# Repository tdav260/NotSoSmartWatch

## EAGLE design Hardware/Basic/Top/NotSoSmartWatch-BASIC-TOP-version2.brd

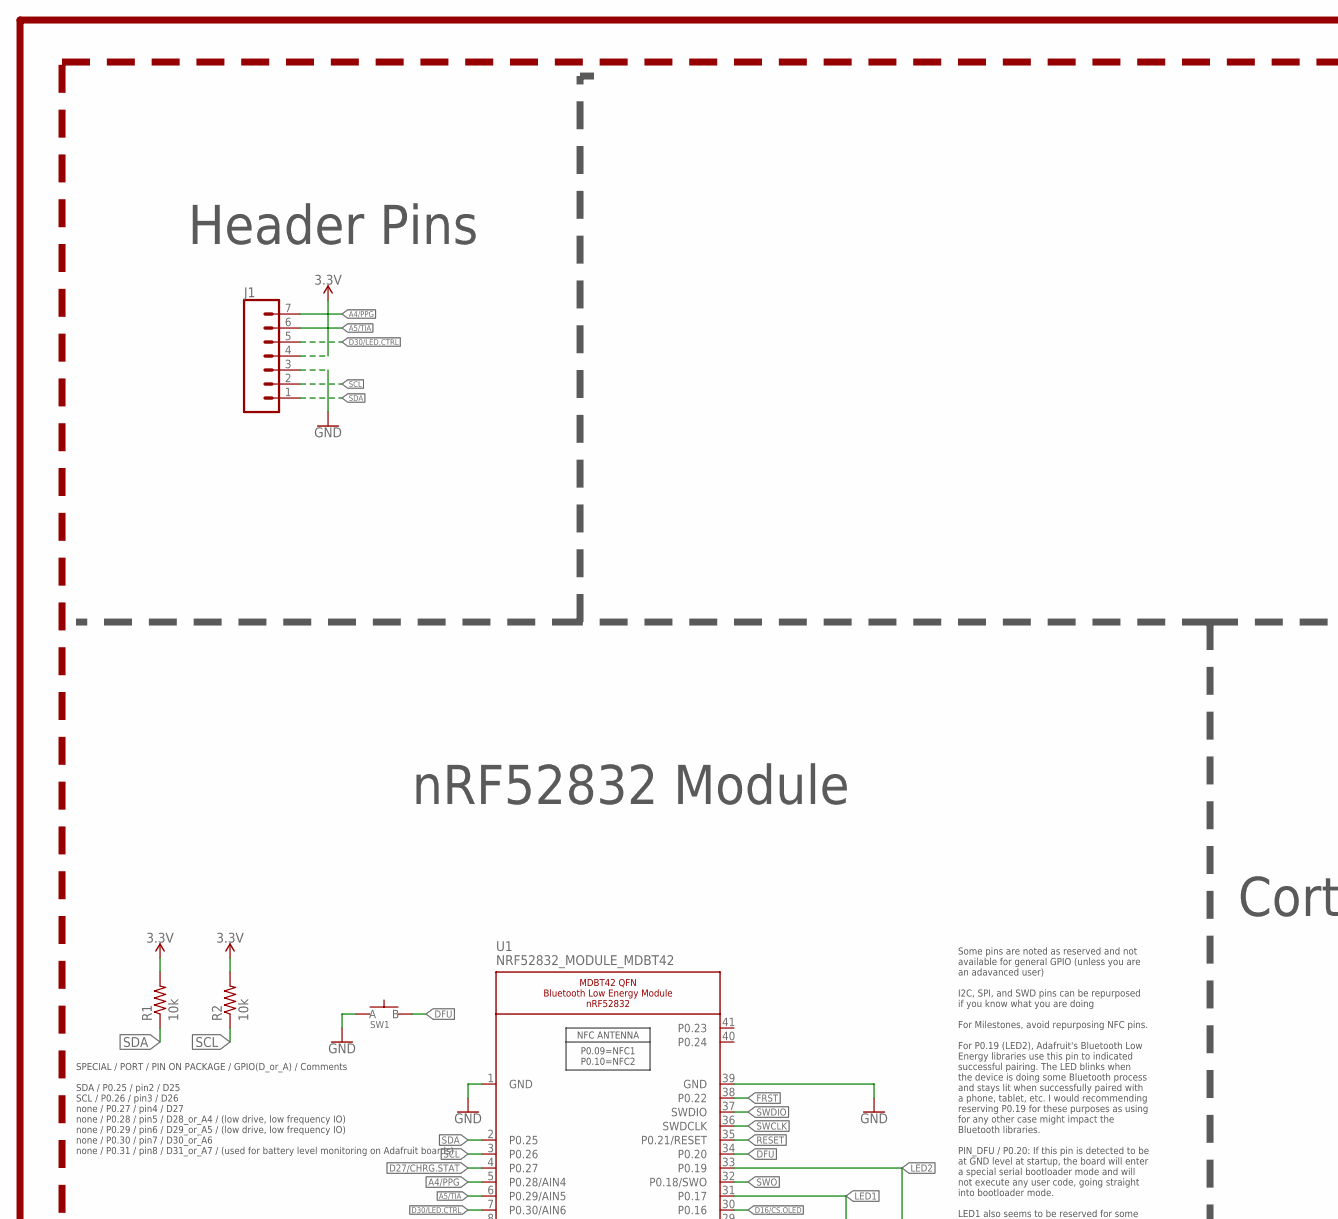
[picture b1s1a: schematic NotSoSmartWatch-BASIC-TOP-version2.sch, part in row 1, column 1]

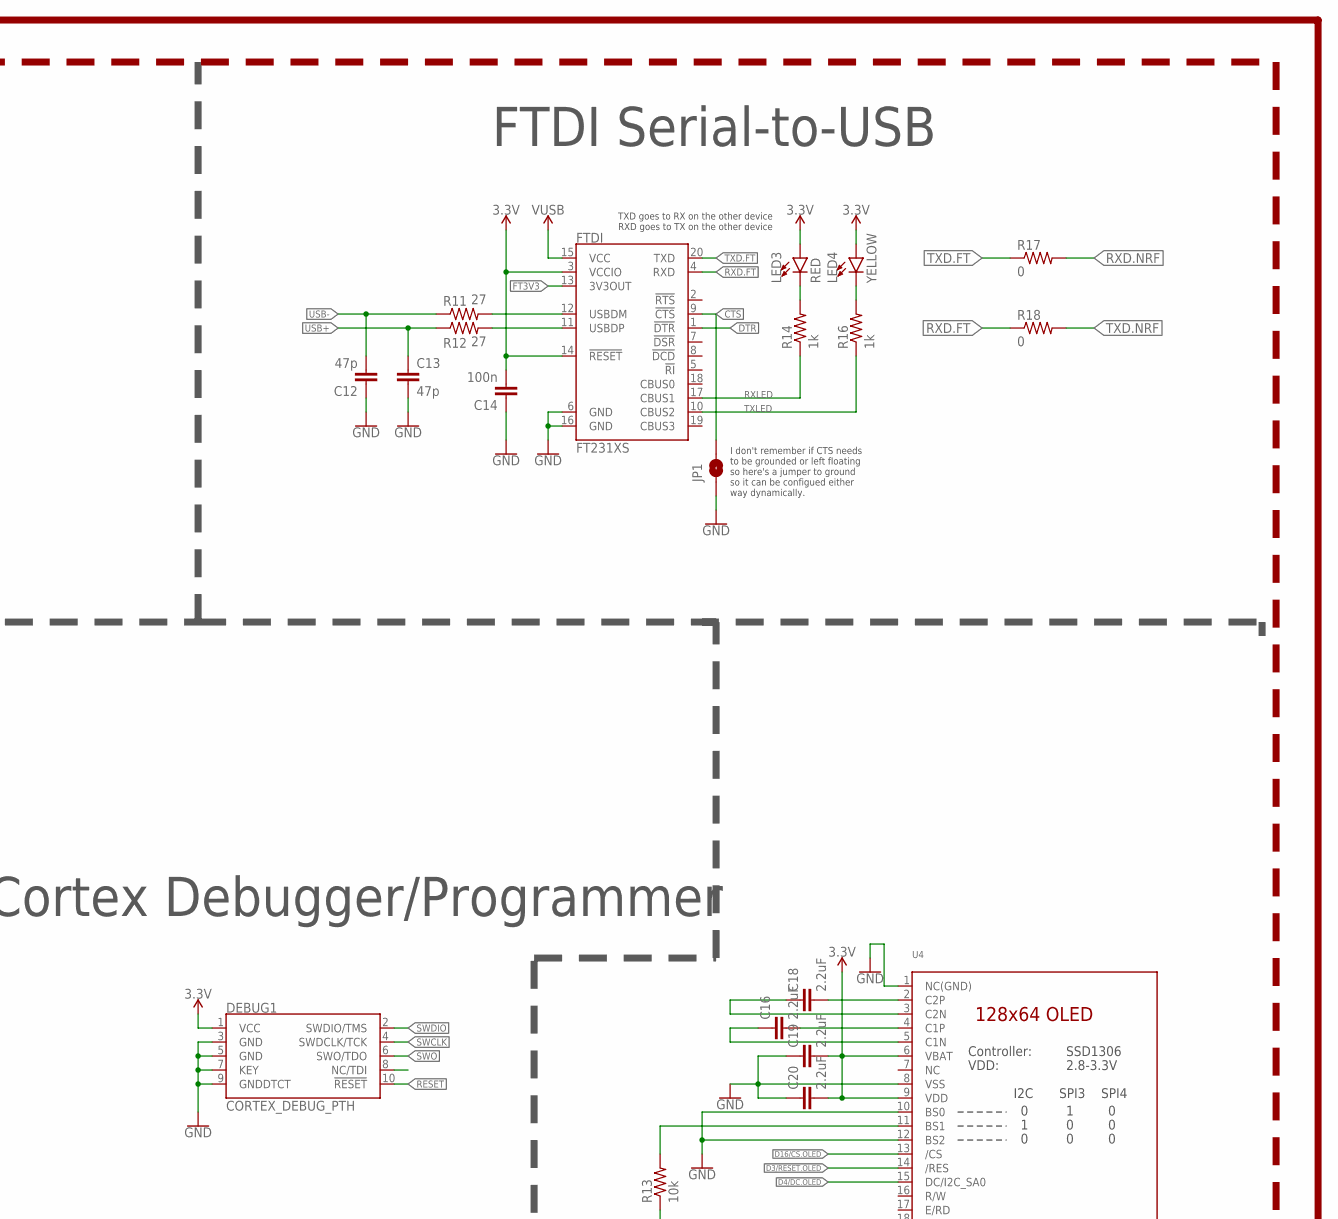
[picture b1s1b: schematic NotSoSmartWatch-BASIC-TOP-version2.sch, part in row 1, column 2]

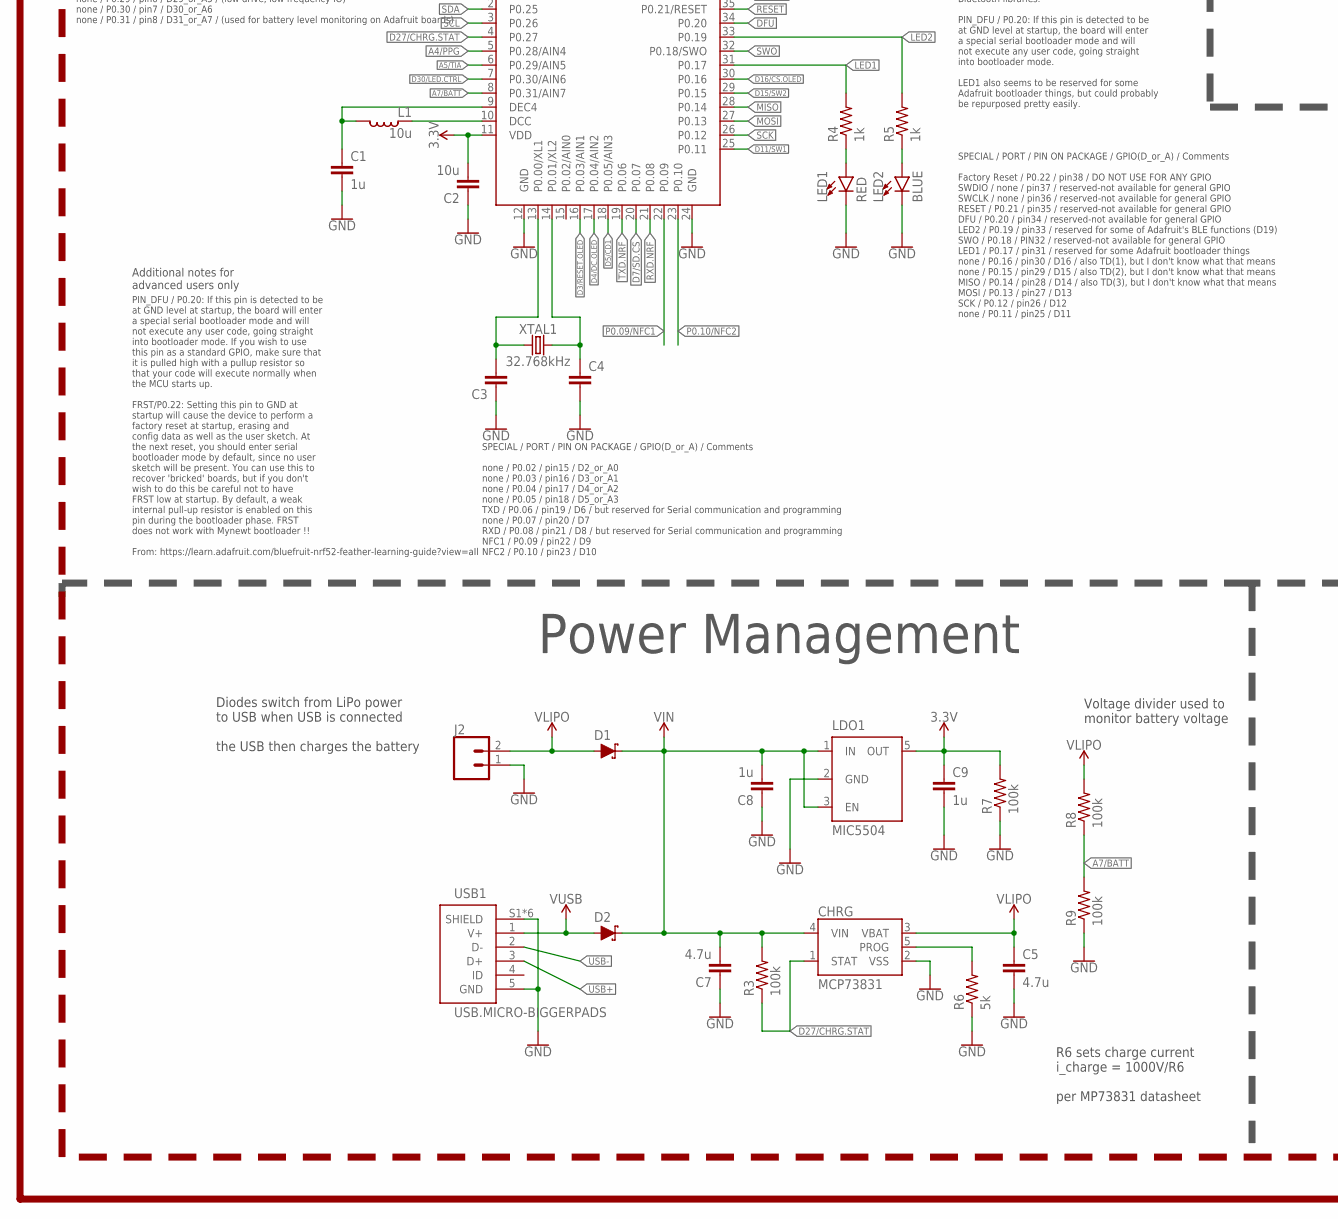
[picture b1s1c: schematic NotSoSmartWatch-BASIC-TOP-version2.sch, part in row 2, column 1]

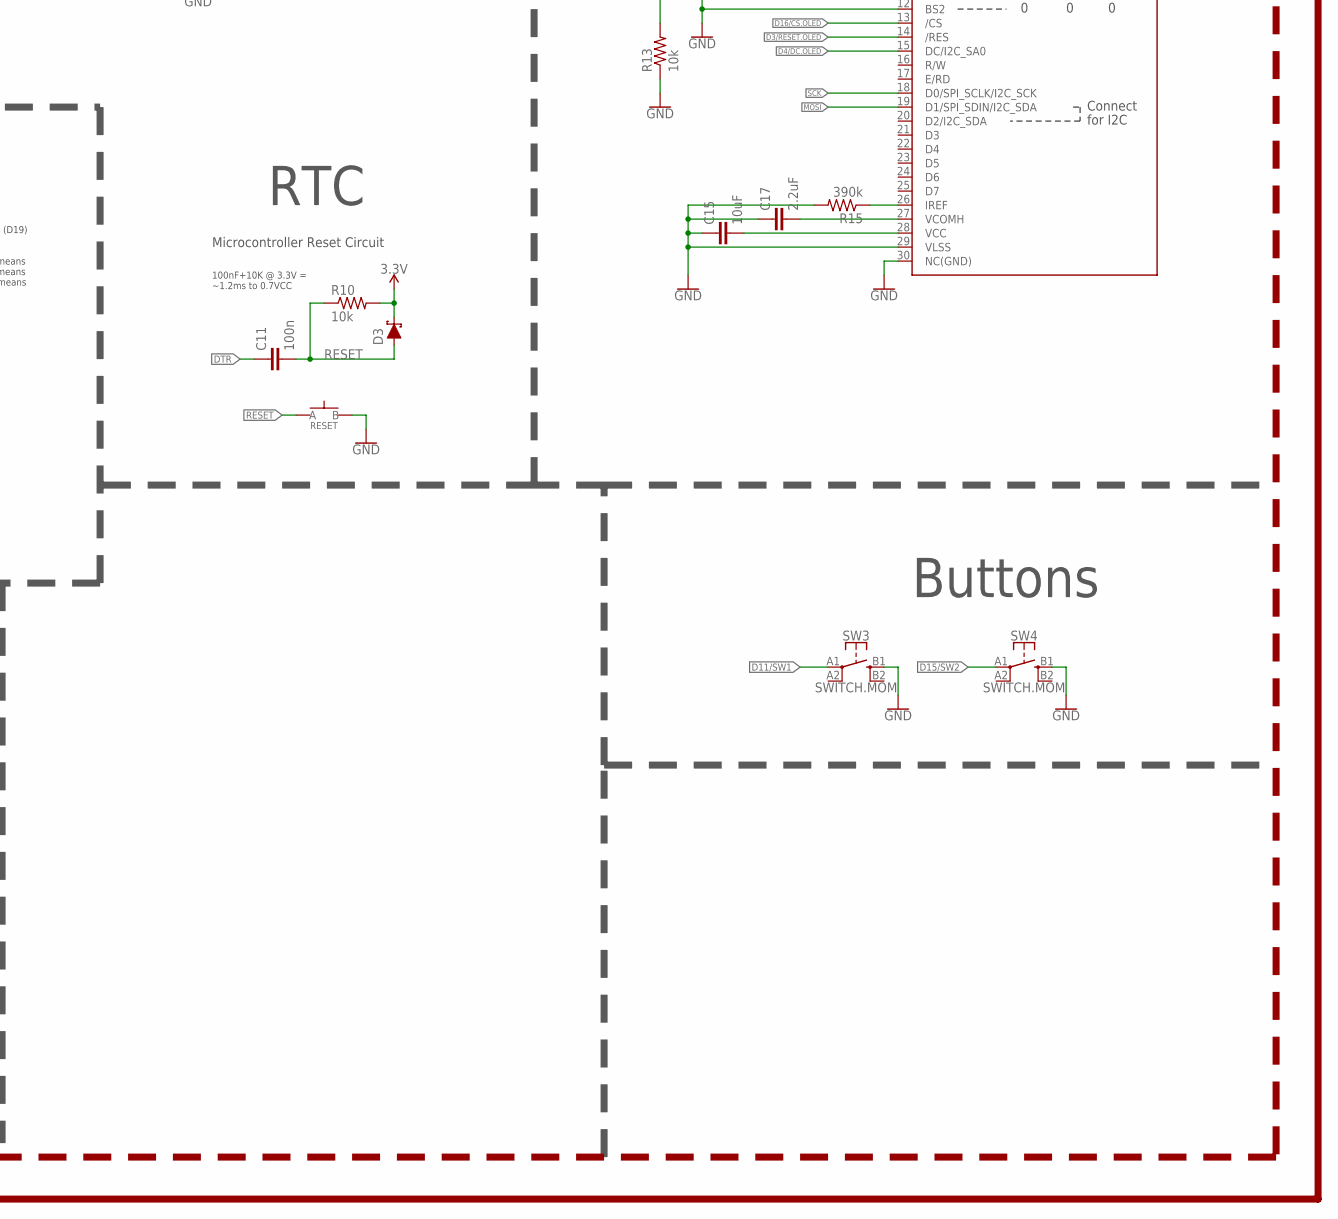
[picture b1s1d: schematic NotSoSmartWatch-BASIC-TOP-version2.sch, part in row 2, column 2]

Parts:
C1, C8, C9: 1u; C0603
C2: 10u; C0805
C3, C4: CAPACITOR0603; C0603
C5, C7: 4.7u; C0603
C11, C14: 100n; C0603
C12, C13: 47p; C0603
C15: 10uF; C0603
C16, C18, C19, C20: 2.2uF; C0402
C17: 2.2uF; C0603
CHRG: MCP73831; SOT23-5
D1, D2, D3: SCHOTTKY-USC; USC
DEBUG1: CORTEX_DEBUG_PTH; 2X5-PTH-1.27MM
FTDI: FT231XS; SSOP20_L
J1: CONN_07-1.27MM; 1X07_1.27MM
J2: CONN_02; 1X02
JP1: JUMPER-SMT_2_NO_SILK; SMT-JUMPER_2_NO_SILK
L1: 10u; L0603
LDO1: MIC5504; SOT23-5
LED1, LED3: RED; LED-0603
LED2: BLUE; LED-0603
LED4: YELLOW; LED-0603
R1, R2, R10, R13: 10k; R0603
R3, R7, R8, R9: 100k; R0603
R4, R5, R14, R16: 1k; R0603
R6: 5k; R0603
R11, R12: 27; R0603
R15: 390k; R0603
R17, R18: 0; R0603
RESET: SPST-PTS830GG140-COPY.1-3; BUTTON-GULLWING
SW1: SPST-PTS830GG140-COPY.1-3; BUTTON-GULLWING
SW3, SW4: SWITCH.MOM; TACTILE_SWITCH_SMD_6.2MM_TALL
U1: NRF52832_MODULE_MDBT42; BLE_MODULE_RAYTAC_MDBT42
U4: DISP_OLED_UG-2864HSWEG01-NO-WRAPAROUND; UG-2864HSWEG01_0.96IN_NO-WRAPAROUND
USB1: USB.MICRO-BIGGERPADS; USB-MICRO-01.BIGGERPADS
XTAL1: 32.768kHz; 2-SMD.NOLEAD.2.0MMTO1.2MM

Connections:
3.3V: C2.2, C9.1, C14.2, C19.2, C20.2, D3.- (C), DEBUG1.1 (VCC), FTDI.3 (VCCIO), FTDI.14 (!RESET), J1.4, LDO1.5 (OUT), LED3.A, LED4.A, R1.2, R2.2, R7.2, R10.2, U1.11 (VDD), U4.6 (VBAT), U4.9 (VDD)
A4/PPG: J1.7, U1.5 (P0.28/AIN4)
A5/TIA: J1.6, U1.6 (P0.29/AIN5)
A7/BATT: R8.1, R9.2, U1.8 (P0.31/AIN7)
CTS: FTDI.9 (!CTS), JP1.2
D3/RESET.OLED: U1.16 (P0.03/AIN1), U4.14 (/RES)
D4/DC.OLED: U1.17 (P0.04/AIN2), U4.15 (DC/I2C_SA0)
D5/CD1: U1.18 (P0.05/AIN3)
D7/SD.CS: U1.20 (P0.07)
D11/SW1: SW3.A1 (1), U1.25 (P0.11)
D15/SW2: SW4.A1 (1), U1.29 (P0.15)
D16/CS.OLED: U1.30 (P0.16), U4.13 (/CS)
D27/CHRG.STAT: CHRG.1 (STAT), R3.1, U1.4 (P0.27)
D30/LED.CTRL: J1.5, U1.7 (P0.30/AIN6)
DFU: SW1.3 (B), U1.34 (P0.20)
DTR: C11.1, FTDI.1 (!DTR)
FRST: U1.38 (P0.22)
FT3V3: FTDI.13 (3V3OUT)
GND: C1.2, C2.1, C3.1, C4.2, C5.2, C7.1, C8.1, C9.2, C12.1, C13.2, C14.1, C15.1, C17.1, C19.1, C20.1, CHRG.2 (VSS), DEBUG1.3 (GND), DEBUG1.5 (GND), DEBUG1.7 (KEY), DEBUG1.9 (GNDDTCT), FTDI.6 (GND), FTDI.16 (GND), J1.3, J2.1, JP1.1, LDO1.2 (GND), LED1.C, LED2.C, R6.1, R7.1, R9.1, R13.1, R15.2, RESET.3 (B), SW1.1 (A), SW3.B1 (3), SW4.B1 (3), U1.1 (GND), U1.12 (GND), U1.24 (GND), U1.39 (GND), U4.1 (NC(GND)), U4.8 (VSS), U4.10 (BS0), U4.12 (BS2), U4.29 (VLSS), U4.30 (NC(GND)), USB1.5 (GND), USB1.S1 (SHIELD), USB1.S2 (SHIELD), USB1.S3 (SHIELD), USB1.S4 (SHIELD), USB1.S5 (SHIELD), USB1.S6 (SHIELD)
LED1: R4.2, U1.31 (P0.17)
LED2: R5.2, U1.33 (P0.19)
MISO: U1.28 (P0.14)
MOSI: U1.27 (P0.13), U4.19 (D1/SPI_SDIN/I2C_SDA)
unnamed: R13.2, U4.11 (BS1)
unnamed: R15.1, U4.26 (IREF)
unnamed: C18.2, U4.2 (C2P)
unnamed: C3.2, U1.13 (P0.00/XL1), XTAL1.P$1 (1)
unnamed: C18.1, U4.3 (C2N)
unnamed: C4.1, U1.14 (P0.01/XL2), XTAL1.P$2 (2)
unnamed: C16.2, U4.4 (C1P)
unnamed: C16.1, U4.5 (C1N)
unnamed: LED1.A, R4.1
unnamed: LED2.A, R5.1
unnamed: L1.1, U1.10 (DCC)
unnamed: C1.1, L1.2, U1.9 (DEC4)
unnamed: C15.2, U4.28 (VCC)
unnamed: C17.2, U4.27 (VCOMH)
unnamed: CHRG.5 (PROG), R6.2
unnamed: FTDI.12 (USBDM), R11.2
unnamed: FTDI.11 (USBDP), R12.2
unnamed: LED3.C, R14.2
unnamed: LED4.C, R16.2
P0.09/NFC1: U1.22 (P0.09)
P0.10/NFC2: U1.23 (P0.10)
RESET: C11.2, D3.+ (A), DEBUG1.10 (!RESET), R10.1, RESET.1 (A), U1.35 (P0.21/RESET)
RXD.FT: FTDI.4 (RXD), R18.1
RXD.NRF: R17.2, U1.21 (P0.08)
RXLED: FTDI.17 (CBUS1), R14.1
SCK: U1.26 (P0.12), U4.18 (D0/SPI_SCLK/I2C_SCK)
SCL: J1.2, R2.1, U1.3 (P0.26)
SDA: J1.1, R1.1, U1.2 (P0.25)
SWCLK: DEBUG1.4 (SWDCLK/TCK), U1.36 (SWDCLK)
SWDIO: DEBUG1.2 (SWDIO/TMS), U1.37 (SWDIO)
SWO: DEBUG1.6 (SWO/TDO), U1.32 (P0.18/SWO)
TXD.FT: FTDI.20 (TXD), R17.1
TXD.NRF: R18.2, U1.19 (P0.06)
TXLED: FTDI.10 (CBUS2), R16.1
USB+: C13.1, R12.1, USB1.3 (D+)
USB-: C12.2, R11.1, USB1.2 (D-)
VIN: C7.2, C8.2, CHRG.4 (VIN), D1.- (C), D2.- (C), LDO1.1 (IN), LDO1.3 (EN), R3.2
VLIPO: C5.1, CHRG.3 (VBAT), D1.+ (A), J2.2, R8.2
V_USB: D2.+ (A), FTDI.15 (VCC), USB1.1 (V+)

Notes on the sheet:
Microcontroller Reset Circuit
100nF+10K @ 3.3V = ~1.2ms to 0.7VCC
SPECIAL / PORT / PIN ON PACKAGE / GPIO(D_or_A) / Comments SDA / P0.25 / pin2 / D25 SCL / P0.26 / pin3 / D26 none / P0.27 / pin4 / D27 none / P0.28 / pin5 / D28_or_A4 / (low drive, low frequency IO) none / P0.29 / pin6 / D29_or_A5 / (low drive, low frequency IO) none / P0.30 / pin7 / D30_or_A6 none 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
SPECIAL / PORT / PIN ON PACKAGE / GPIO(D_or_A) / Comments none / P0.02 / pin15 / D2_or_A0 none / P0.03 / pin16 / D3_or_A1 none / P0.04 / pin17 / D4_or_A2 none / P0.05 / pin18 / D5_or_A3 TXD / P0.06 / pin19 / D6 / but reserved for Serial communication and programming none / P0.07 / pin20 / D7 RXD / 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
SPECIAL / PORT / PIN ON PACKAGE / GPIO(D_or_A) / Comments Factory Reset / P0.22 / pin38 / DO NOT USE FOR ANY GPIO SWDIO / none / pin37 / reserved-not available for general GPIO SWCLK / none / pin36 / reserved-not available for general GPIO RESET / P0.21 / pin35 / reserved-not available for general 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
Some pins are noted as reserved and not available for general GPIO (unless you are an adavanced user) I2C, SPI, and SWD pins can be repurposed if you know what you are doing For Milestones, avoid repurposing NFC pins. For P0.19 (LED2), Adafruit's Bluetooth Low Energy libraries use this pin to indic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
PIN_DFU / P0.20: If this pin is detected to be at GND level at startup, the board will enter a special serial bootloader mode and will not execute any user code, going straight into bootloader mode. If you wish to use this pin as a standard GPIO, make sure that it is pulled high with a pullup resis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
Additional notes for advanced users only
nRF52832 Module
Power Management
Buttons
Cortex Debugger/Programmer
RTC
TXD goes to RX on the other device RXD goes to TX on the other device
I don't remember if CTS needs to be grounded or left floating so here's a jumper to ground so it can be configued either way dynamically.
FTDI Serial-to-USB
Header Pins
Diodes switch from LiPo power to USB when USB is connected the USB then charges the battery
R6 sets charge current i_charge = 1000V/R6 per MP73831 datasheet
Voltage divider used to monitor battery voltage

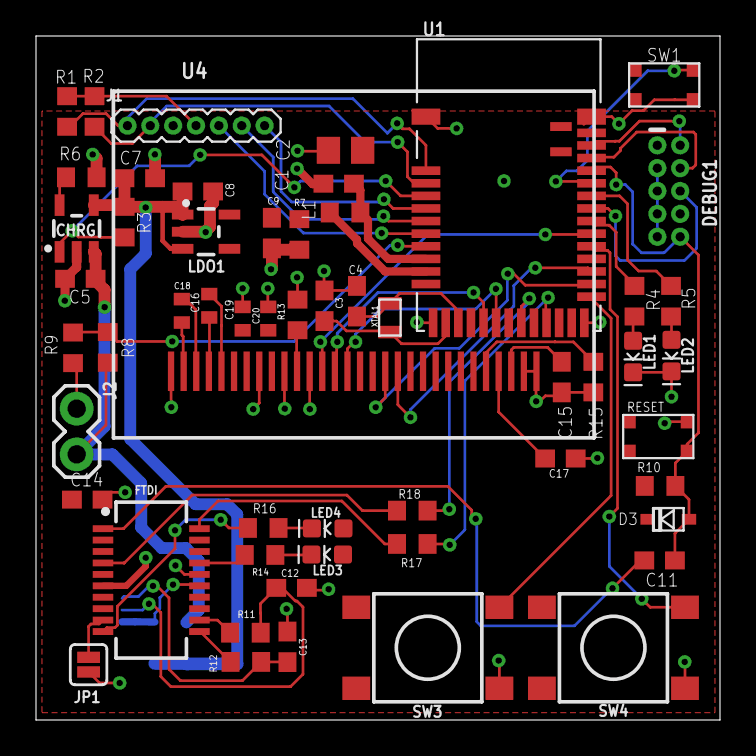
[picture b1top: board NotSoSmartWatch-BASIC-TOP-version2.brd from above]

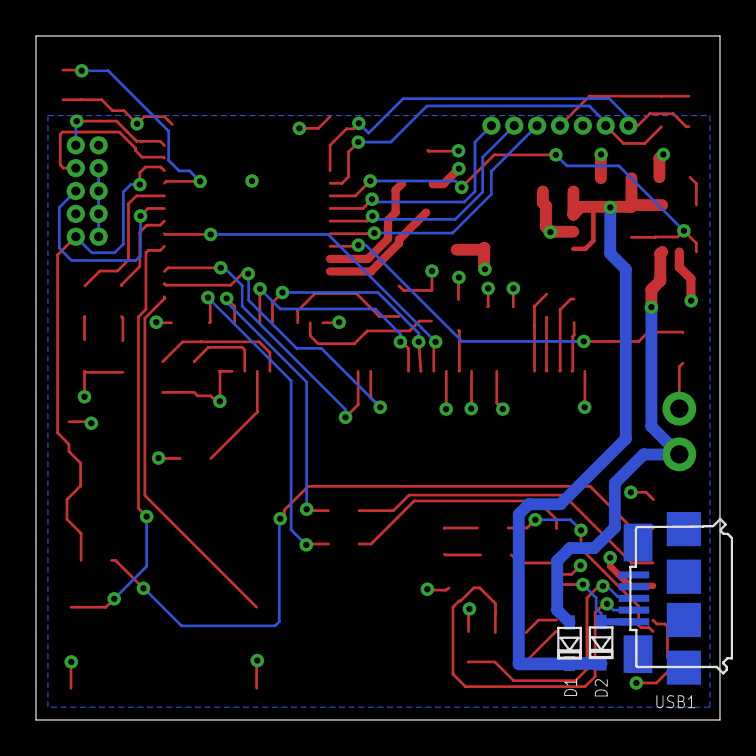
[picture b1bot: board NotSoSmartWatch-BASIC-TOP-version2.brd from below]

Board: 2 copper layers, 38.0 x 38.0 mm, 59 parts (3 on the bottom side), 55 nets.

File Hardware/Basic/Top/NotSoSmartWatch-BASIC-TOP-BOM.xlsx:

NotSoSmartWatch Top Board -- Rev A / Thomas Davis |  |  |  |  |  |  |  |  |  |  | Total | 23.845800000000001 | Total (in Bulk) | 2.2500999999999998
BOM # | Comment | Designator | Description | Mounting Type | Package | Manufacturer | Manufacturer Part Number | Supplier | Supplier Part Number | Price per unit | Quantity | Total | Per 100 | Total
 | DigiKey
1 | Microcontroller | U1 | Bluetooth Bluetooth v4.2 Transceiver Module 2.4GHz Integrated, Chip Surface Mou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 | SMD | 41-SMD Module | Seeed Technology Co., Ltd | 317030213 | Digi-Key | 1597-1434-ND | 10.1 | 1 | 10.1
2 | FTDI | FTDI | USB Bridge, USB to UART USB 2.0 UART Interface 20-SSOP | SMD | 20-SSOP | FTDI, Future Technology Devices International Ltd | FT231XS-U | Digi-Key | 768-1156-5-ND | 2.12 | 1 | 2.12 | 1.98 | 1.98
3 | USB Interface | USB1 | USB - micro B USB 2.0 Receptacle Connector 5 Position Surface Mount, Right Angle | SMD | Flange, Horizontal | Amphenol FCI | 10118192-0001LF | Digi-Key | 609-4613-1-ND | 0.43 | 1 | 0.43
4 | Battery Charger | CHRG | Charger IC Lithium-Ion/Polymer SOT-23-5 | SMD | SOT-23-5 | Microchip Technology | MCP73831T-2ACI/OT | Digi-Key | MCP73831T-2ACI/OTCT-ND | 0.56000000000000005 | 1 | 0.56000000000000005
5 | Voltage Regulator | LDO1 | Linear Voltage Regulator IC 1 Output 300mA SOT-23-5 | SMD | SOT23-5 | Microchip Technology | MIC5504-3.3YM5-TR | Digi-Key | 576-4764-1-ND | 0.11 | 1 | 0.11 | 0.08 | 0.08
6 | Bigger Button | SW3, SW4 | Tactile Switch SPST-NO Top Actuated Surface Mount | SMD | Gull Wing | C&K | PTS645SM43SMTR92 LFS | Digi-Key | CKN9112CT-ND | 0.25 | 2 | 0.5
7 | 390k ohm resistor | R15 | 390 kOhms ±1% 0.1W, 1/10W Chip Resistor 0603 (1608 Metric) Automotive AEC-Q200 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 | SMD | 0603 | Stackpole Electronics Inc | RMCF0603FG390K | Digi-Key | RMCF0603FG390KCT-ND | 5.8999999999999999E-3 | 1 | 5.8999999999999999E-3
8 | Schottky Diode | D1, D2, D3 | Diode Schottky 30V 1.5A Surface Mount USC | SMD | USC | Toshiba Semiconductor and Storage | CUS15S30,H3F | Digi-Key | CUS15S30H3FCT-ND | 0.25600000000000001 | 3 | 0.76800000000000002
9 | 100 nF Capacitor | C11, C14 | 0.1µF ±5% 16V Ceramic Capacitor X7R 0603 (1608 Metric) | SMD | 0603 | Yageo | CC0603JRX7R7BB104 | Digi-Key | 311-1776-1-ND | 3.3099999999999997E-2 | 2 | 6.6199999999999995E-2
10 | 10k ohm Resistor | R1, R2, R6, R10, R13 | 10 kOhms ±1% 0.1W, 1/10W Chip Resistor 0603 (1608 Metric) Automotive AEC-Q200 T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 | SMD | 0603 | Stackpole Electronics Inc | RMCF0603FT10K0 | Digi-Key | RMCF0603FT10K0CT-ND | 5.8999999999999999E-3 | 5 | 2.9499999999999998E-2
11 | 2.2u capacitor | C16, C17, C18, C19, C20 | 2.2µF ±10% 16V Ceramic Capacitor X5R 0603 (1608 Metric) | SMD | 0603 | Samsung Electro-Mechanics | CL10A225KO8NNNC | Digi-Key | 1276-1040-1-ND | 3.1600000000000003E-2 | 5 | 0.15800000000000003
12 | 10 uF 0603 Capacitor | C2, C15 | 10µF ±10% 10V Ceramic Capacitor X5R 0603 (1608 Metric) | SMD | 0603 | Murata Electronics | GRM188R61A106KE69J | Digi-Key | 490-14372-1-ND | 6.3200000000000006E-2 | 2 | 0.12640000000000001
13 | 47 pF Capacitor | C12, C13 | 47pF ±5% 50V Ceramic Capacitor C0G, NP0 0603 (1608 Metric) | SMD | 0603 | Walsin Technology Corporation | 0603N470J500CT | Digi-Key | 1292-1528-1-ND | 1.0999999999999999E-2 | 2 | 2.1999999999999999E-2
14 | 27 ohm resistor | R11, R12 | 27 Ohms ±1% 0.1W, 1/10W Chip Resistor 0603 (1608 Metric) Automotive AEC-Q200 Th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 | SMD | 0603 | Stackpole Electronics Inc | RMCF0603FT27R0 | Digi-Key | RMCF0603FT27R0CT-ND | 5.8999999999999999E-3 | 2 | 1.18E-2
15 | 1k ohm Resistor | R4, R5, R14, R16 | 1 kOhms ±1% 0.1W, 1/10W Chip Resistor 0603 (1608 Metric) Automotive AEC-Q200 Th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 | SMD | 0603 | Stackpole Electronics Inc | RMCF0603FT1K00 | Digi-Key | RMCF0603FT1K00CT-ND | 5.8999999999999999E-3 | 4 | 2.3599999999999999E-2
16 | Red LED | LED1, LED3 | Red 622nm LED Indication - Discrete 2.2V 0603 (1608 Metric) | SMD | 0603 | Inolux | IN-S63ATR | Digi-Key | 1830-1065-1-ND | 0.17699999999999999 | 2 | 0.35399999999999998
17 | Yellow LED | LED4 | Yellow 590nm LED Indication - Discrete 2V 0603 (1608 Metric) | SMD | 0603 | Wurth Electronics Inc. | 150060YS75000 | Digi-Key | 732-4981-1-ND | 0.14000000000000001 | 1 | 0.14000000000000001
18 | Blue LED | LED2 | Blue 470nm LED Indication - Discrete 3V 0603 (1608 Metric) | SMD | 0603 | Inolux | IN-S63AT5B | Digi-Key | 1830-1061-1-ND | 0.17699999999999999 | 1 | 0.17699999999999999
19 | 32.768 kHz Crystal | XTAL1 | 32.768kHz ±10ppm Crystal 12.5pF 90 kOhms 2-SMD, No Lead | SMD | 2-SMD, No Lead | ECS Inc. | ECS-.327-12.5-12-C-TR | Digi-Key | XC2288CT-ND | 0.59799999999999998 | 1 | 0.59799999999999998
20 | 12 pF Capacitor | C3, C4 | 12pF ±5% 50V Ceramic Capacitor C0G, NP0 0603 (1608 Metric) | SMD | 0603 | Walsin Technology Corporation | 0603N120J500CT | Digi-Key | 1292-1480-1-ND | 1.1900000000000001E-2 | 2 | 2.3800000000000002E-2
21 | Debugger | DEBUG1 | Connector Header Through Hole 10 position 0.050" (1.27mm) | THT | NA | Amphenol ICC (FCI) | 20021111-00010T4LF | Digi-Key | 609-3712-ND | 0.69 | 1 | 0.69
22 | 1 uF Capacitor | C1, C8, C9 | 1µF ±10% 25V Ceramic Capacitor X5R 0603 (1608 Metric) | SMD | 0603 | Samsung Electro-Mechanics | CL10A105KA8NNNC | Digi-Key | 1276-1102-1-ND | 0.1 | 3 | 0.30000000000000004 | 1.8499999999999999E-2 | 5.5499999999999994E-2
23 | 10 uH Inductor | L1 | 10µH Shielded Multilayer Inductor 250mA 1.05Ohm 0603 (1608 Metric) | SMD | 0603 | TDK Corporation | MLZ1608M100WTD25 | Digi-Key | MLZ1608M100WTD25 | 0.22 | 1 | 0.22 | 0.1346 | 0.1346
24 | 4.7 uF Capacitor | C5, C7 | 4.7 uF ±10% 16V Ceramic Capacitor X5R 0603 (1608 Metric) | SMD | 0603 | Samsung Electro-Mechanics | CL10A475KO8NNNC | Digi-Key | 1276-1784-1-ND | 4.3999999999999997E-2 | 2 | 8.7999999999999995E-2
25 | 100k ohm Resistor | R3, R7, R8, R9 | 100 kOhms ±1% 0.1W, 1/10W Chip Resistor 0603 (1608 Metric) Automotive AEC-Q200 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 | SMD | 0603 | Stackpole Electronics Inc | RMCF0603FT100K | Digi-Key | RMCF0603FT100KCT-ND | 5.8999999999999999E-3 | 4 | 2.3599999999999999E-2
26 | CONN_07-1.27MM (CONN_07) | J1 | 50 Position Header Connector 0.050" (1.27mm) Through Hole Gold | THT |  | Sullins Connector Solutions | LPPB501NFFN-RC | Digi-Key | S9008E-50-ND | 5.0599999999999996 | 1 | 5.0599999999999996
27 | Tiny Rectangular Switch | SW1, RESET | Tactile Switch SPST-NO Top Actuated Surface Mount | SMD | Gull Wing | C&K Components | PTS830GM140 SMTR LFS | Digi-Key | CKN10587CT-ND | 0.56999999999999995 | 2 | 1.1399999999999999
28 | Header Pins - 2 | J2
 | BuyDisplay.com
29 | OLED | U4 | Datasheet 128x64 OLED Module SPI 0.96"Graphic Displays,White on Black | SMD | Flexible Connector | EastRising | https://www.buydisplay.com/datasheet-128x64-oled-module-spi-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 | BuyDisplay.com | https://www.buydisplay.com/datasheet-128x64-oled-module-spi-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 | 2.5099999999999998

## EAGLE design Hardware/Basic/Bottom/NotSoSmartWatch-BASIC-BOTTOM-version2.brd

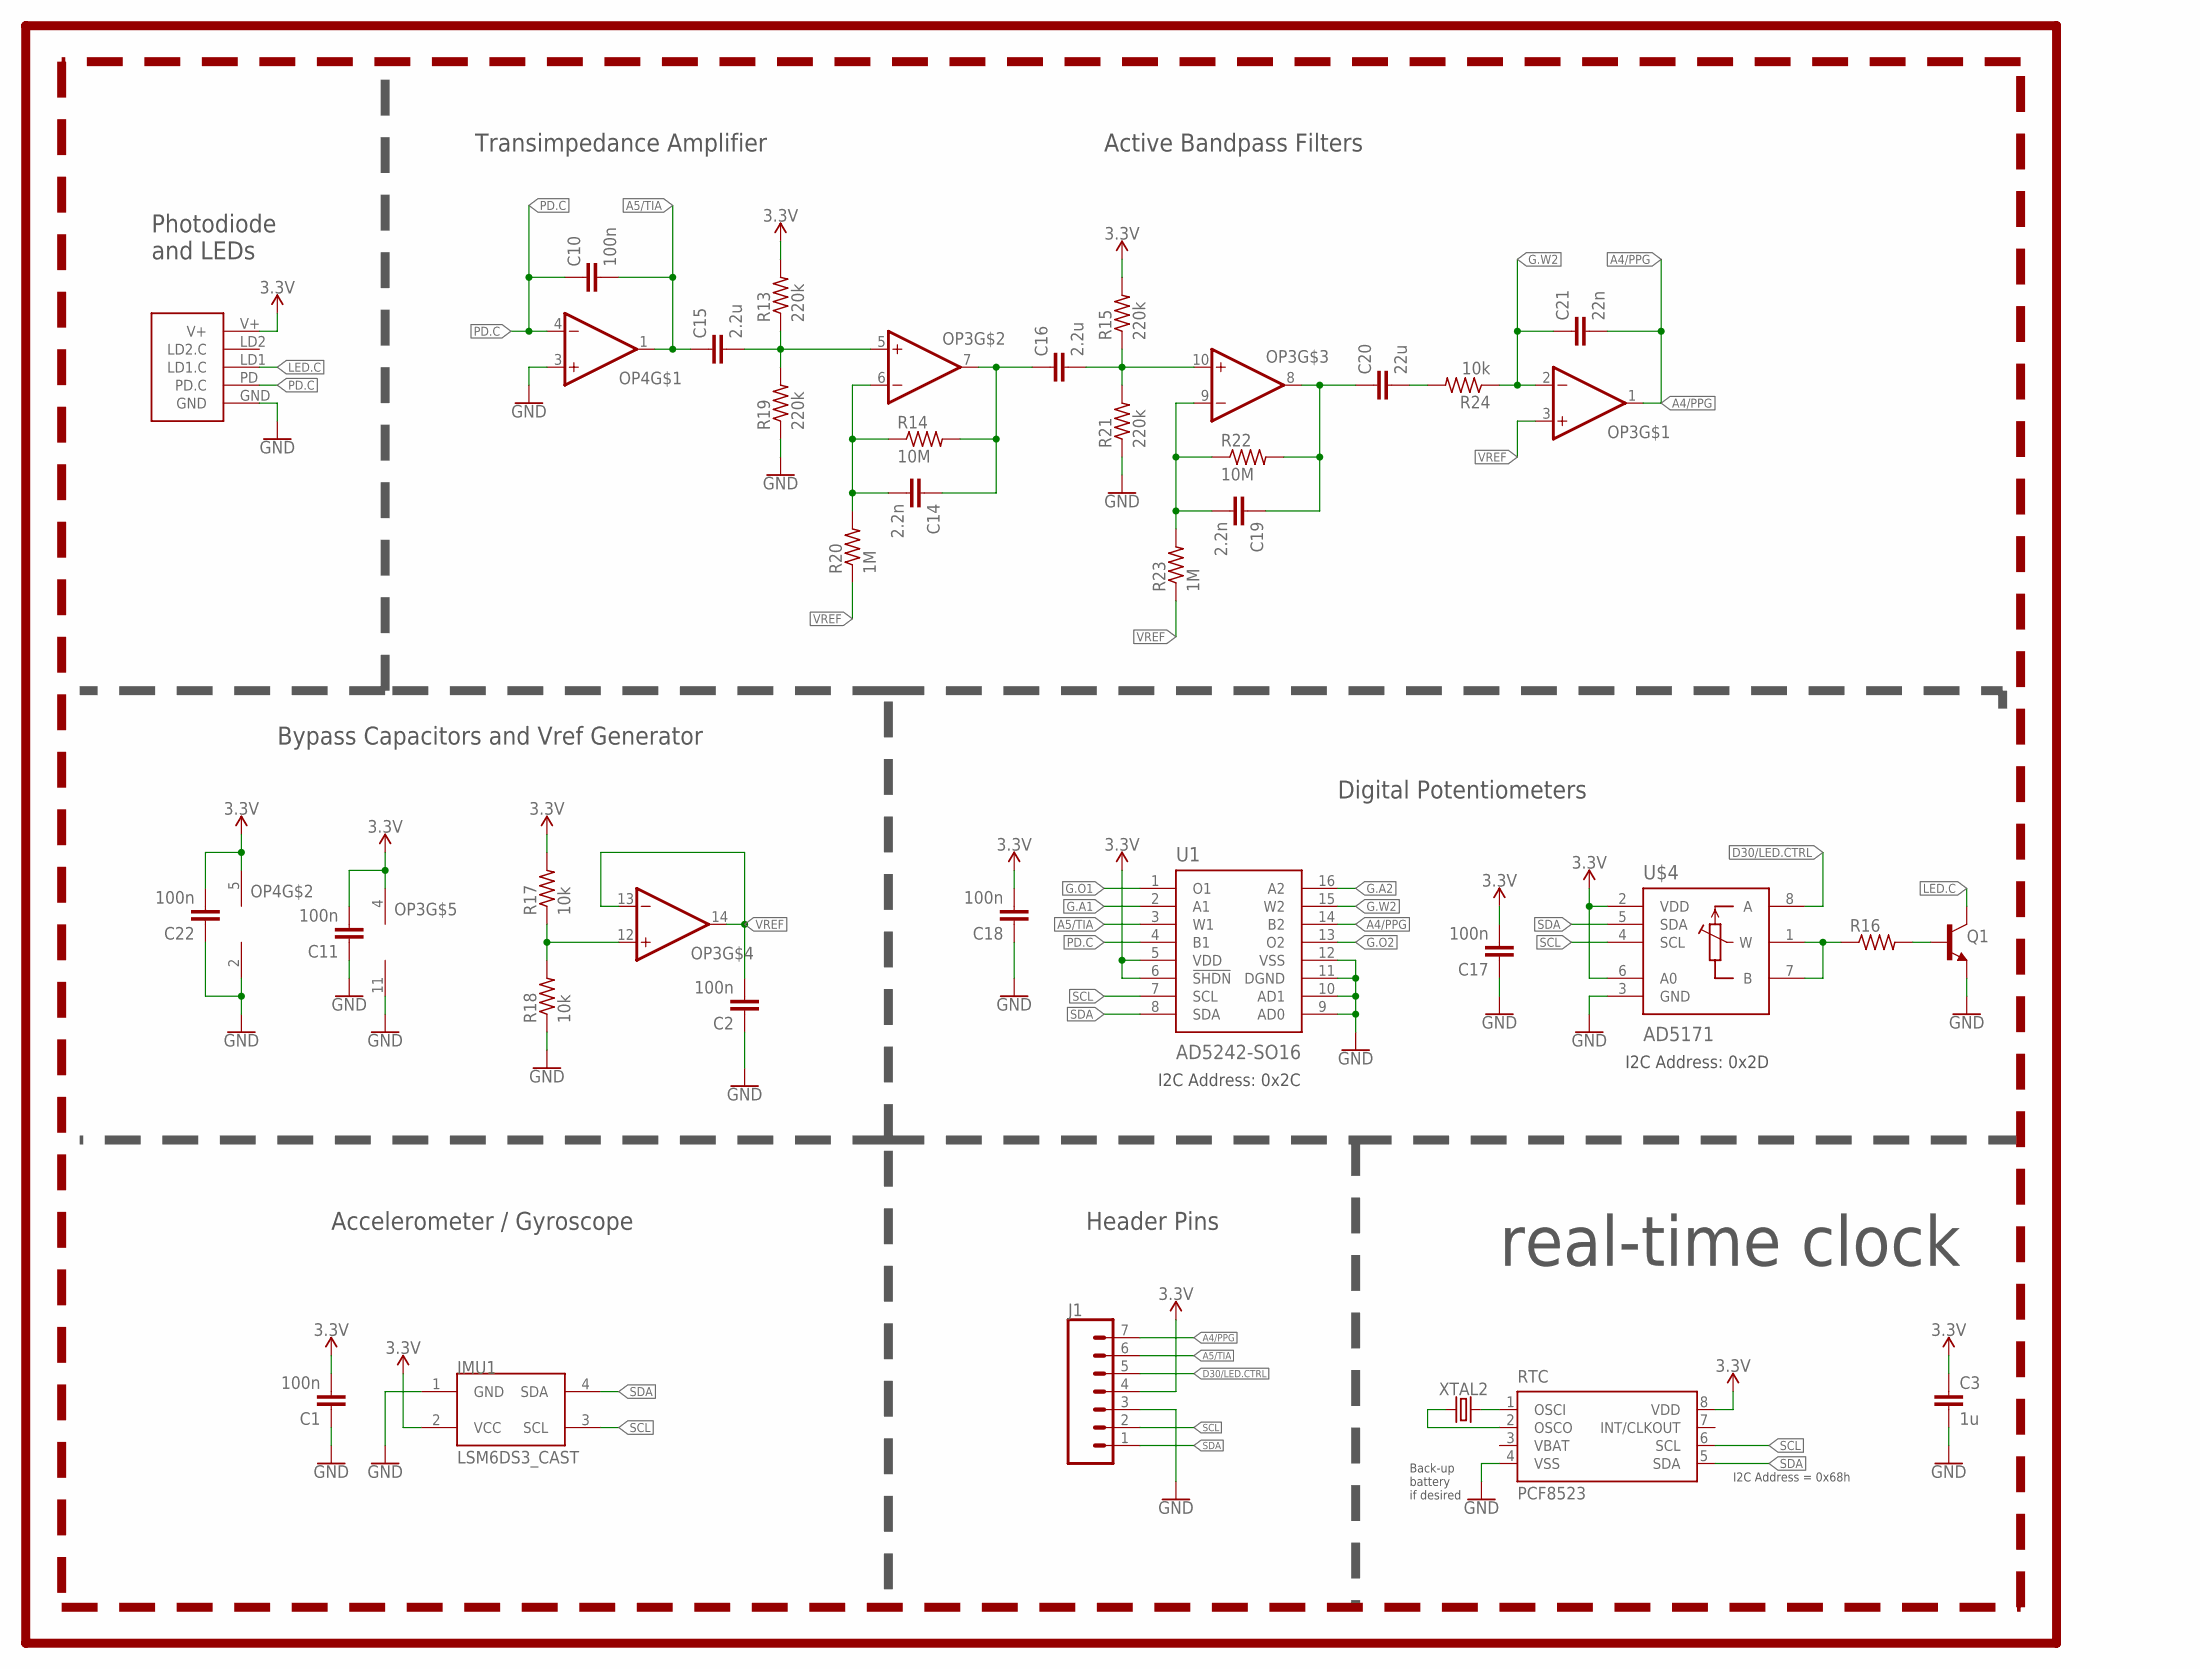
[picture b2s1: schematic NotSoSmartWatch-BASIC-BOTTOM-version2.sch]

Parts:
C1, C2, C10, C11, C17, C18, C22: 100n; C0603
C3: 1u; C0603
C14, C19: 2.2n; C0603
C15, C16: 2.2u; C0603
C20: 22u; C0603
C21: 22n; C0603
IMU1: LSM6DS3_CAST
J1: CONN_07-1.27MM; 1X07_1.27MM
OP3: OP-QUAD-SO14; SO14
OP4: OP-SINGLEOT; SOT23-5
Q1: NPN-GENERIC; SOT23-3
R13, R15, R19, R21: 220k; R0603
R14, R22: 10M; R0603
R16: RESISTOR0603; R0603
R17, R18: 10k; R0402
R20, R23: 1M; R0603
R24: 10k; R0603
RTC: PCF8523; SO8; DIGIKEY 568-5306-1-ND
U1: AD5242-SO16; SO16
U$3: PPG.MODULE.2
U$4: AD5171; SOT-23-8
XTAL2: 32.7680kHz; 2-SMD.NOLEAD.2.0MMTO1.2MM

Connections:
3.3V: C1.2, C3.1, C11.2, C17.2, C18.2, C22.2, IMU1.2 (VCC), J1.4, OP3.4 (V+), OP4.5 (V+), R13.2, R15.2, R17.2, RTC.8 (VDD), U1.5 (VDD), U1.6 (!SHDN), U$3.V+, U$4.2 (VDD), U$4.6 (A0)
A4/PPG: C21.2, J1.7, OP3.1 (OUT), U1.14 (B2)
A5/TIA: C10.2, C15.1, J1.6, OP4.1 (OUT), U1.3 (W1)
D30/LED.CTRL: J1.5, U$4.8 (A)
G.A1: U1.2 (A1)
G.A2: U1.16 (A2)
G.O1: U1.1 (O1)
G.O2: U1.13 (O2)
G.W2: C21.1, OP3.2 (-IN), R24.1, U1.15 (W2)
GND: C1.1, C2.1, C3.2, C11.1, C17.1, C18.1, C22.1, IMU1.1 (GND), J1.3, OP3.11 (V-), OP4.2 (V-), OP4.3 (+IN), Q1.2 (E), R18.1, R19.1, R21.1, RTC.4 (VSS), U1.9 (AD0), U1.10 (AD1), U1.11 (DGND), U1.12 (VSS), U$3.GND, U$4.3 (GND)
LED.C: Q1.3 (C), U$3.LD1 (LD1.C)
unnamed: Q1.1 (B), R16.2
unnamed: R16.1, U$4.1 (W), U$4.7 (B)
unnamed: OP3.12 (+IN), R17.1, R18.2
unnamed: RTC.2 (OSCO), XTAL2.P$1 (1)
unnamed: RTC.1 (OSCI), XTAL2.P$2 (2)
unnamed: C15.2, OP3.5 (+IN), R13.1, R19.2
unnamed: C14.2, OP3.6 (-IN), R14.1, R20.2
unnamed: C14.1, C16.1, OP3.7 (OUT), R14.2
unnamed: C16.2, OP3.10 (+IN), R15.1, R21.2
unnamed: C19.2, OP3.9 (-IN), R22.1, R23.2
unnamed: C19.1, C20.1, OP3.8 (OUT), R22.2
unnamed: C20.2, R24.2
PD.C: C10.1, OP4.4 (-IN), U1.4 (B1), U$3.PD (PD.C)
SCL: IMU1.3 (SCL), J1.2, RTC.6 (SCL), U1.7 (SCL), U$4.4 (SCL)
SDA: IMU1.4 (SDA), J1.1, RTC.5 (SDA), U1.8 (SDA), U$4.5 (SDA)
VBAT: RTC.3 (VBAT)
VREF: C2.2, OP3.3 (+IN), OP3.13 (-IN), OP3.14 (OUT), R20.1, R23.1

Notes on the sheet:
Photodiode and LEDs
Active Bandpass Filters
Digital Potentiometers
Transimpedance Amplifier
I2C Address: 0x2C
I2C Address: 0x2D
Header Pins
Accelerometer / Gyroscope
Bypass Capacitors and Vref Generator
I2C Address = 0x68h
Back-up battery if desired
real-time clock

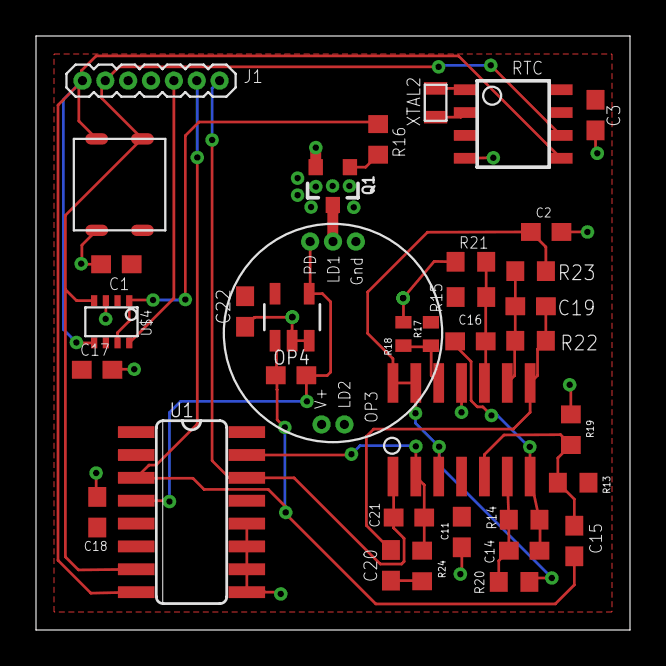
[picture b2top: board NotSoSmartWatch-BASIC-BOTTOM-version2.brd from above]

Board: 2 copper layers, 33.0 x 33.0 mm, 36 parts (0 on the bottom side), 23 nets.

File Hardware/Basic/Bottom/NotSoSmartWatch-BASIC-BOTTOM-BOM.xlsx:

NotSoSmartWatch Bottom Board -- Rev A / Thomas Davis |  |  |  |  |  |  |  |  |  |  | Total | 83.733700000000013 | Total (in Bulk) | 5.5499999999999994E-2
BOM # | Comment | Designator | Description | Mounting Type | Package | Manufacturer | Manufacturer Part Number | Supplier | Supplier Part Number | Price per unit | Quantity | Total | Per 100 | Total
 | DigiKey
1 | Real-Time Clock | RTC | Real Time Clock (RTC) IC Clock/Calendar I²C, 2-Wire Serial 8-SOIC (0.154", 3.90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 | SMD | 8-SO | NXP USA Inc. | PCF8523T/1,118 | Digi-Key | 568-5306-1-ND | 1.26 | 1 | 1.26
2 | 32.768 kHz Crystal | XTAL2 | 32.768kHz ±10ppm Crystal 12.5pF 90 kOhms 2-SMD, No Lead | SMD | 2-SMD, No Lead | ECS Inc. | ECS-.327-12.5-12-C-TR | Digi-Key | XC2288CT-ND | 0.59799999999999998 | 1 | 0.59799999999999998
3 | AD5242 | U1 | Digital Potentiometer 1M Ohm 2 Circuit 256 Taps I²C Interface 16-SOIC | SMD | 16-SOIC | Analog Devices Inc. | AD5242BRZ1M | Digi-Key | AD5242BRZ1M-ND | 3.47 | 6 | 20.82
4 | CONN_07-1.27MM (CONN_07) | J1 | 50 Position Header Connector 0.050" (1.27mm) Through Hole Gold | THT |  | Sullins Connector Solutions | LPPB501NFFN-RC | Digi-Key | S9008E-50-ND | 5.0599999999999996 | 1 | 5.0599999999999996
5 | NPN-Generic | Q1 | Bipolar (BJT) Transistor NPN 40V 600mA 300MHz 250mW Surface Mount TO-236AB | SMD | TO-236AB | Nexperia USA Inc. | PMBT2222A,215 | Digi-Key | 1727-2956-1-ND | 1.05 | 10 | 10.5
6 | 100 nF Capacitor | C1, C2, C10, C11, C17, C18, C22 | 0.1µF ±5% 16V Ceramic Capacitor X7R 0603 (1608 Metric) | SMD | 0603 | Yageo | CC0603JRX7R7BB104 | Digi-Key | 311-1776-1-ND | 3.3099999999999997E-2 | 2 | 6.6199999999999995E-2
7 | 10k ohm Resistor | R17, R18, R24 | 10 kOhms ±1% 0.1W, 1/10W Chip Resistor 0603 (1608 Metric) Automotive AEC-Q200 T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 | SMD | 0603 | Stackpole Electronics Inc | RMCF0603FT10K0 | Digi-Key | RMCF0603FT10K0CT-ND | 5.8999999999999999E-3 | 5 | 2.9499999999999998E-2
8 | 1 uF Capacitor | C3 | 1µF ±10% 25V Ceramic Capacitor X5R 0603 (1608 Metric) | SMD | 0603 | Samsung Electro-Mechanics | CL10A105KA8NNNC | Digi-Key | 1276-1102-1-ND | 0.1 | 3 | 0.30000000000000004 | 1.8499999999999999E-2 | 5.5499999999999994E-2
9 | CONN_07-1.27MM | G$1 | 50 Positions Header Connector 0.050" (1.27mm) Through Hole Gold | THT |  | Sullins Connector Solutions | GRPB501VWVN-RC | Digi-Key | S9014E-50-ND | 3.11 | 5 | 15.549999999999999
10 | 2.2 uF Capacitor | C14, C15, C16, C19 | 2.2µF ±10% 16V Ceramic Capacitor X5R 0603 (1608 Metric) | SMD | 0603 | Samsung Electro-Mechanics | CL10A225KO8NNNC | Digi-Key | 1276-1040-1-ND | 3.1600000000000003E-2 | 100 | 3.16 |  | 0
11 | 220k ohm Resistor | R13, R15, R19, R21 | 220 kOhms ±1% 0.1W, 1/10W Chip Resistor 0603 (1608 Metric) Automotive AEC-Q200 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 | SMD | 0603 | Stackpole Electronics Inc | RMCF0603FT220K | Digi-Key | RMCF0603FT220KCT-ND | 5.8999999999999999E-3 | 100 | 0.59
12 | 10M ohm Resistor | R14, R22 | 10 MOhms ±1% 0.1W, 1/10W Chip Resistor 0603 (1608 Metric) Automotive AEC-Q200 T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 | SMD | 0603 | Stackpole Electronics Inc | RMCF0603FT10M0 | Digi-Key | RMCF0603FT10M0CT-ND | 8.8999999999999999E-3 | 100 | 0.89
13 | 1M ohm Resistor | R20, R23 | 1 MOhms ±1% 0.1W, 1/10W Chip Resistor 0603 (1608 Metric) Automotive AEC-Q200 Th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 | SMD | 0603 | Stackpole Electronics Inc | RMCF0603FT1M00 | Digi-Key | RMCF0603FT1M00CT-ND | 5.8999999999999999E-3 | 100 | 0.59
14 | 22 uF Capacitor | C20 | 22µF ±20% 10V Ceramic Capacitor X5R 0603 (1608 Metric) | SMD | 0603 | Samsung Electro-Mechanics | CL10A226MP8NUNE | Digi-Key | 1276-1274-1-ND | 6.7199999999999996E-2 | 100 | 6.72 |  | 0
15 | 22 nF Capacitor | C21 | 0.022µF ±10% 50V Ceramic Capacitor X7R 0603 (1608 Metric) | SMD | 0603 | Samsung Electro-Mechanics | CL10B223KB8NNNC | Digi-Key | 1276-1104-1-ND | 1.5599999999999999E-2 | 100 | 1.5599999999999998
16 | Op Amp | OP3$G1, OP3$G2, OP3$G3, OP3$G4, OP4$G1 | General Purpose Amplifier 4 Circuit Rail-to-Rail 14-SOIC | SMD | 14-SOIC | Microchip Technology | MCP6004T-I/SL | Digi-Key | MCP6004T-I/SLCT-ND | 0.44 | 6 | 2.64
 | Mouser
1 | AD5171 | U$4 | Digital Potentiometer ICs IC 6-Bit OTP I2C | SMD | SOT-23-8 | Analog Devices | AD5171BRJZ100-R7 | Mouser | 584-AD5171BRJZ100-R7 | 2.68 | 5 | 13.4 |  | 0
 | Custom Order
1 | LSM6DS3 castellated breakout | IMU1 |  |  |  |  |  |  |  |  |  | 0
